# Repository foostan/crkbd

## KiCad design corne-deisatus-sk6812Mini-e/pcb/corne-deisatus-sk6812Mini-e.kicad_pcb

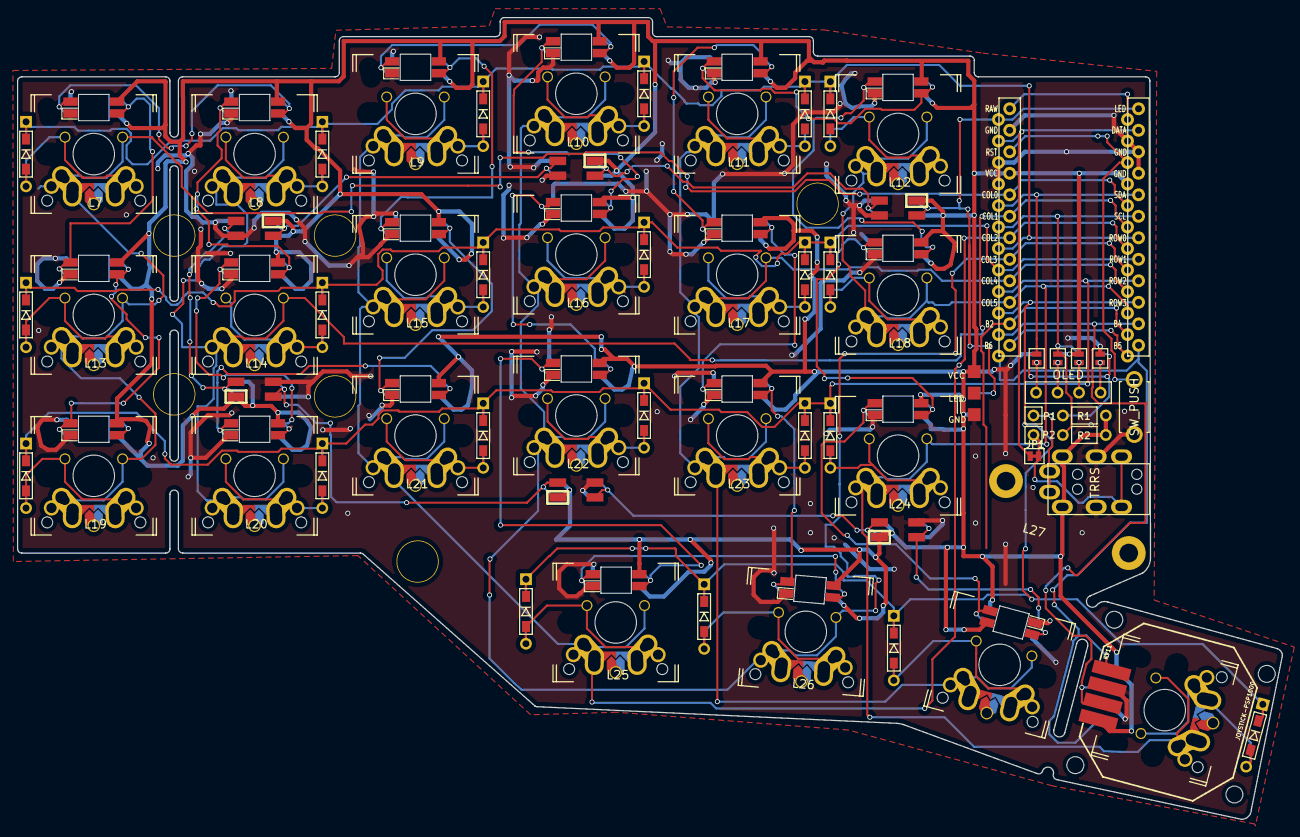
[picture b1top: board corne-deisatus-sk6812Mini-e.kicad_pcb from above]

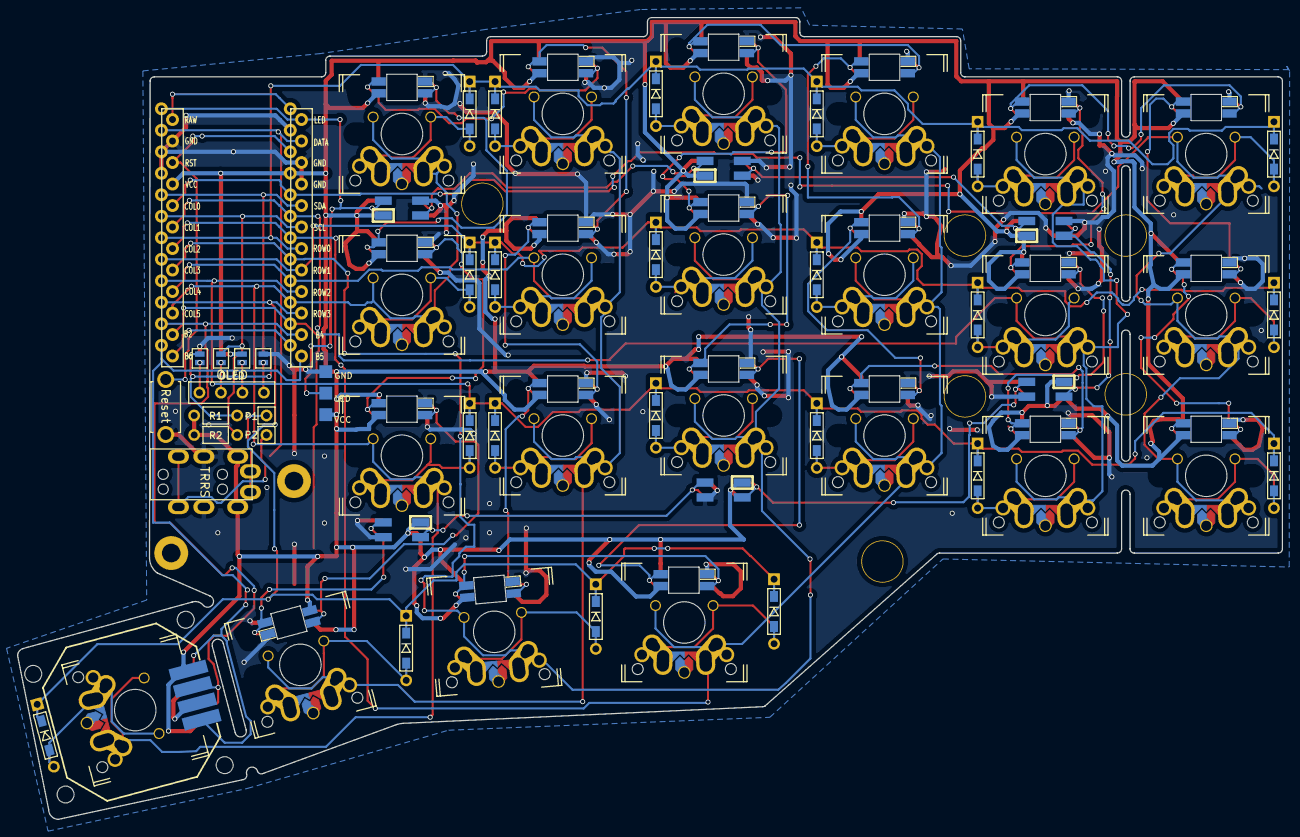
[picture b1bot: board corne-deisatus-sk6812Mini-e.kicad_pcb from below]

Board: 2 copper layers, 149.4 x 94.7 mm, 90 parts (4 on the bottom side), 73 nets.

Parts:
D1, D2, D3, D4, D5, D6, D7, D8, D9, D10, D11, D12, D13, D14, D15, D16, D17, D18, D19, D20, D21, D22: D; D3_TH_SMD
J1: MJ-4PP-9
J2: OLED
J3: LED; StripLED_rev
JP1: JP
JP2, JP3, JP4, JP5, JP6, JP7, JP8, JP9: Jumper
L1, L2, L3, L4, L5, L6: SK6812MINI; SK6812MINI_underglow_rev
L7, L8, L9, L10, L11, L12, L13, L14, L15, L16, L17, L18, L19, L20, L21, L22, L23, L24, L25, L26, L27: SK6812MINI-E; YS-SK6812MINI-E
P1, P2: i2c-pin; 1pin_conn
R1, R2: R
RSW1: SW_PUSH; ResetSW
RV11: JOYSTICK-PSP1000; JOYSTICK-PSP1000-reverse
SW1, SW2, SW3, SW4, SW5, SW6, SW7, SW8, SW9, SW10, SW11, SW12, SW13, SW14, SW15, SW16, SW17, SW18, SW19, SW21, SW22: SW_PUSH; MX-ALPS-Choc-X-straight-crane2
SW20: SW_PUSH; MX-ALPS-Choc-X-straight-crane2-u1.25
U1: ProMicro; ProMicro_v2

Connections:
AnalogX: RV11.1, U1.12
AnalogY: RV11.3, U1.11
GND: J1.C, J3.1, JP2.1, JP9.1, L1.2, L2.2, L3.2, L4.2, L5.2, L6.2, L7.3, L8.3, L9.3, L10.3, L11.3, L12.3, L13.3, L14.3, L15.3, L16.3, L17.3, L18.3, L19.3, L20.3, L21.3, L22.3, L23.3, L24.3, L25.3, L26.3, L27.3, RSW1.2, RV11.2, U1.3, U1.4, U1.23
LED: J3.2, L3.3, U1.1
unnamed: D1.2, SW1.2
unnamed: D2.2, SW2.2
unnamed: D3.2, SW3.2
unnamed: D4.2, SW4.2
unnamed: D5.2, SW5.2
unnamed: D6.2, SW6.2
unnamed: D7.2, SW7.2
unnamed: D8.2, SW8.2
unnamed: D9.2, SW9.2
unnamed: D10.2, SW10.2
unnamed: D11.2, SW11.2
unnamed: D12.2, SW12.2
unnamed: D13.2, SW13.2
unnamed: D14.2, SW14.2
unnamed: D15.2, SW15.2
unnamed: D16.2, SW16.2
unnamed: D17.2, SW17.2
unnamed: D18.2, SW18.2
unnamed: D19.2, SW20.2
unnamed: D20.2, SW21.2
unnamed: D21.2, SW22.2
unnamed: D22.2, SW19.2
unnamed: J1.A, P1.1
unnamed: J1.B, JP1.2, P2.1
unnamed: J2.1, JP5.2, JP9.2
unnamed: J2.2, JP4.2, JP8.2
unnamed: J2.3, JP3.2, JP7.2
unnamed: J2.4, JP2.2, JP6.2
unnamed: L1.1, L4.3
unnamed: L1.3, L2.1
unnamed: L2.3, L3.1
unnamed: L4.1, L5.3
unnamed: L5.1, L6.3
unnamed: L7.4, L8.2
unnamed: L9.4, L10.2
unnamed: L10.4, L16.2
unnamed: L11.2, L17.4
unnamed: L11.4, L12.2
unnamed: L12.4, L18.2
unnamed: L13.2, L19.4
unnamed: L7.2, L13.4
unnamed: L8.4, L14.2
unnamed: L14.4, L20.2
unnamed: L15.2, L21.4
unnamed: L9.2, L15.4
unnamed: L16.4, L22.2
unnamed: L17.2, L23.4
unnamed: L18.4, L24.2
unnamed: L20.4, L21.2
unnamed: L22.4, L25.2
unnamed: L23.2, L26.4
unnamed: L24.4, L27.2
unnamed: L25.4, L26.2
unnamed: L6.1, L27.4
SCL: JP4.1, JP7.1, R2.2, U1.6
SDA: JP5.1, JP6.1, R1.2, U1.5
VCC: J1.D, J3.3, JP3.1, JP8.1, L1.4, L2.4, L3.4, L4.4, L5.4, L6.4, L7.1, L8.1, L9.1, L10.1, L11.1, L12.1, L13.1, L14.1, L15.1, L16.1, L17.1, L18.1, L19.1, L20.1, L21.1, L22.1, L23.1, L24.1, L25.1, L26.1, L27.1, R1.1, R2.1, RV11.4, U1.21
col0: SW1.1, SW7.1, SW13.1, U1.20
col1: SW2.1, SW8.1, SW14.1, U1.19
col2: SW3.1, SW9.1, SW15.1, SW19.1, U1.18
col3: SW4.1, SW10.1, SW16.1, SW20.1, U1.17
col4: SW5.1, SW11.1, SW17.1, SW21.1, U1.16
col5: SW6.1, SW12.1, SW18.1, SW22.1, U1.15
data: JP1.1, U1.2
reset: RSW1.1, U1.22
row0: D1.1, D2.1, D3.1, D4.1, D5.1, D6.1, U1.7
row1: D7.1, D8.1, D9.1, D10.1, D11.1, D12.1, U1.8
row2: D13.1, D14.1, D15.1, D16.1, D17.1, D18.1, U1.9
row3: D19.1, D20.1, D21.1, D22.1, U1.10
